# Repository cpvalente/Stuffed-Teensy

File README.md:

Kicad libraries from here 
https://github.com/XenGi/teensy_library

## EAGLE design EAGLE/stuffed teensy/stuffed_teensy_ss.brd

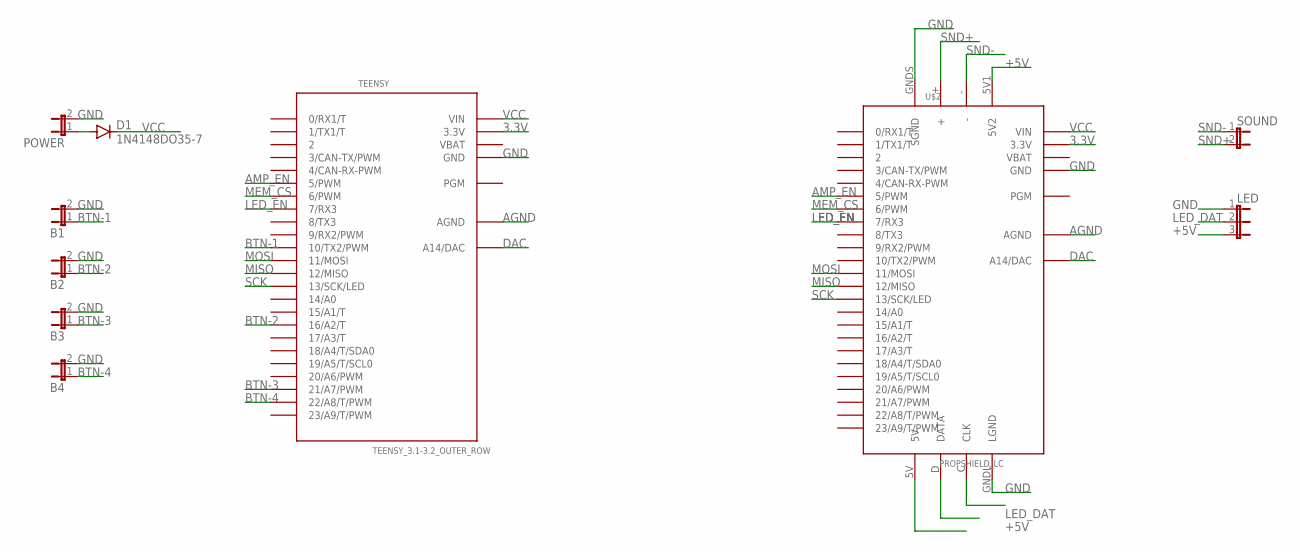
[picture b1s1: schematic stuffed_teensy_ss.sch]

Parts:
B1, B2, B3, B4: JP1E; JP1
D1: 1N4148DO35-7; DO35-7
LED: JP2E; JP2
POWER: JP1E; JP1
SOUND: JP1E; JP1
TEENSY: TEENSY_3.1-3.2_OUTER_ROW; TEENSY_3.0-3.2&LC_OUTER_ROW
U$2: PROPSHIELD_LC; TEENSY_PROPSHIELD_LC

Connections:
3.3V: TEENSY.3.3V, TEENSY.3.3V1 (3.3V), U$2.3.3V, U$2.3.3V1 (3.3V)
+5V: LED.3, U$2.5V, U$2.5V1 (5V2)
AGND: TEENSY.AGND, U$2.AGND
AMP_EN: TEENSY.5 (5/PWM), U$2.5 (5/PWM)
BTN-1: B1.1, TEENSY.10 (10/TX2/PWM)
BTN-2: B2.1, TEENSY.16/A2 (16/A2/T)
BTN-3: B3.1, TEENSY.21/A7 (21/A7/PWM)
BTN-4: B4.1, TEENSY.22/A8 (22/A8/T/PWM)
DAC: TEENSY.RESET/DAC (A14/DAC), U$2.RESET/DAC (A14/DAC)
GND: B1.2, B2.2, B3.2, B4.2, LED.1, POWER.2, TEENSY.GND, TEENSY.GND1 (GND), U$2.GND, U$2.GND1 (GND), U$2.GNDL (LGND), U$2.GNDS (SGND)
LED_DAT: LED.2, U$2.D (DATA)
LED_EN: TEENSY.7 (7/RX3), U$2.7 (7/RX3)
MEM_CS: TEENSY.6 (6/PWM), U$2.6 (6/PWM)
MISO: TEENSY.12 (12/MISO), U$2.12 (12/MISO)
MOSI: TEENSY.11 (11/MOSI), U$2.11 (11/MOSI)
SCK: TEENSY.13 (13/SCK/LED), U$2.13 (13/SCK/LED)
SND+: SOUND.2, U$2.+
SND-: SOUND.1, U$2.-
VBAT: TEENSY.VBAT, U$2.VBAT
VCC: D1.C, TEENSY.VIN, U$2.VIN
VCC_: D1.A, POWER.1

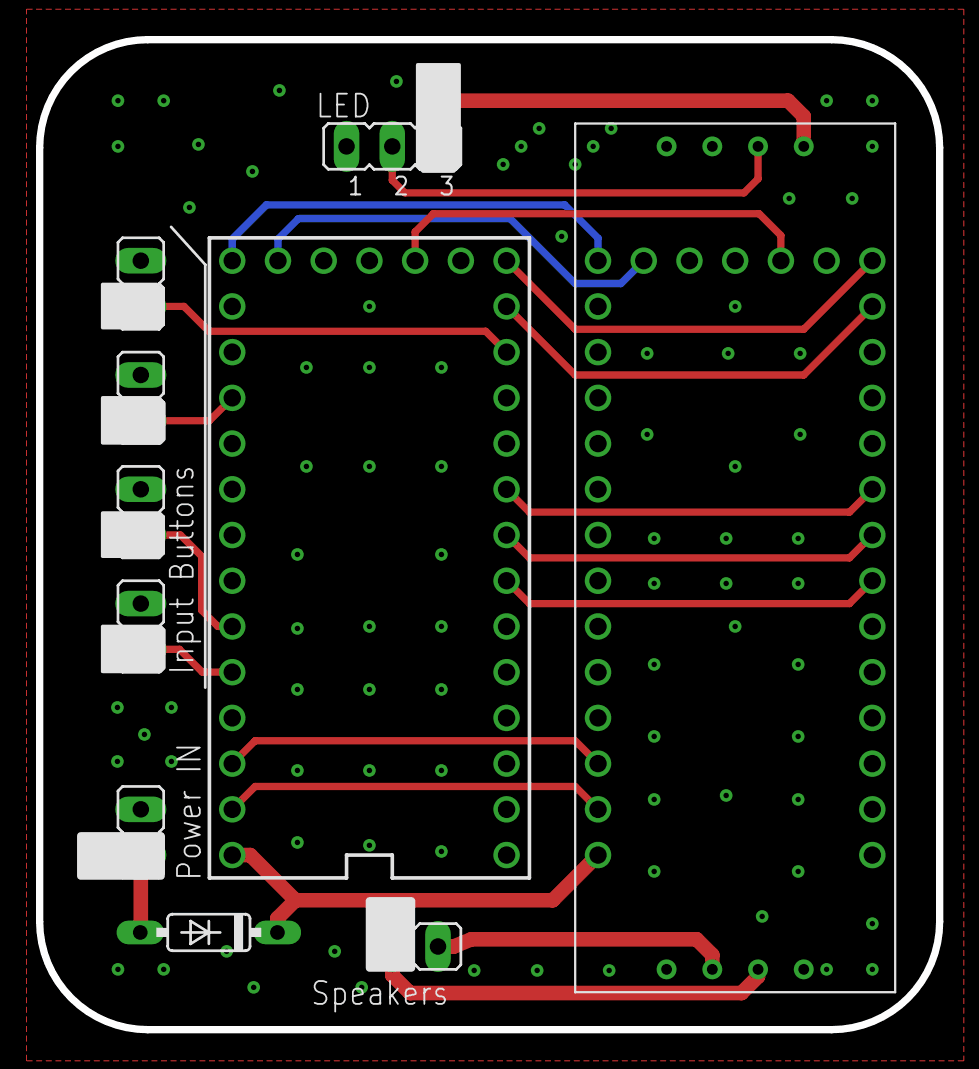
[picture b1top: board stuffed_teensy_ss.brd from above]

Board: 2 copper layers, 50.0 x 55.0 mm, 10 parts (0 on the bottom side), 21 nets.
